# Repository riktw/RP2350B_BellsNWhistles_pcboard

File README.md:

## PCBoard for RP2350B BellsNWhistles

This contains the kicad files for a little board that turns the [RP2350B BellsNWhistles](https://github.com/riktw/RP2350B_BellsNWhistles) board into a small computer.
It has all the modern and some retro IO like:

- 3 x USB
- PS/2 for mouse and keyboard
- NES controller
- Audio via 3.5mm
- MicroSD for storage
- On board RTC

This board is tested and no bugs should remain in the latest version.

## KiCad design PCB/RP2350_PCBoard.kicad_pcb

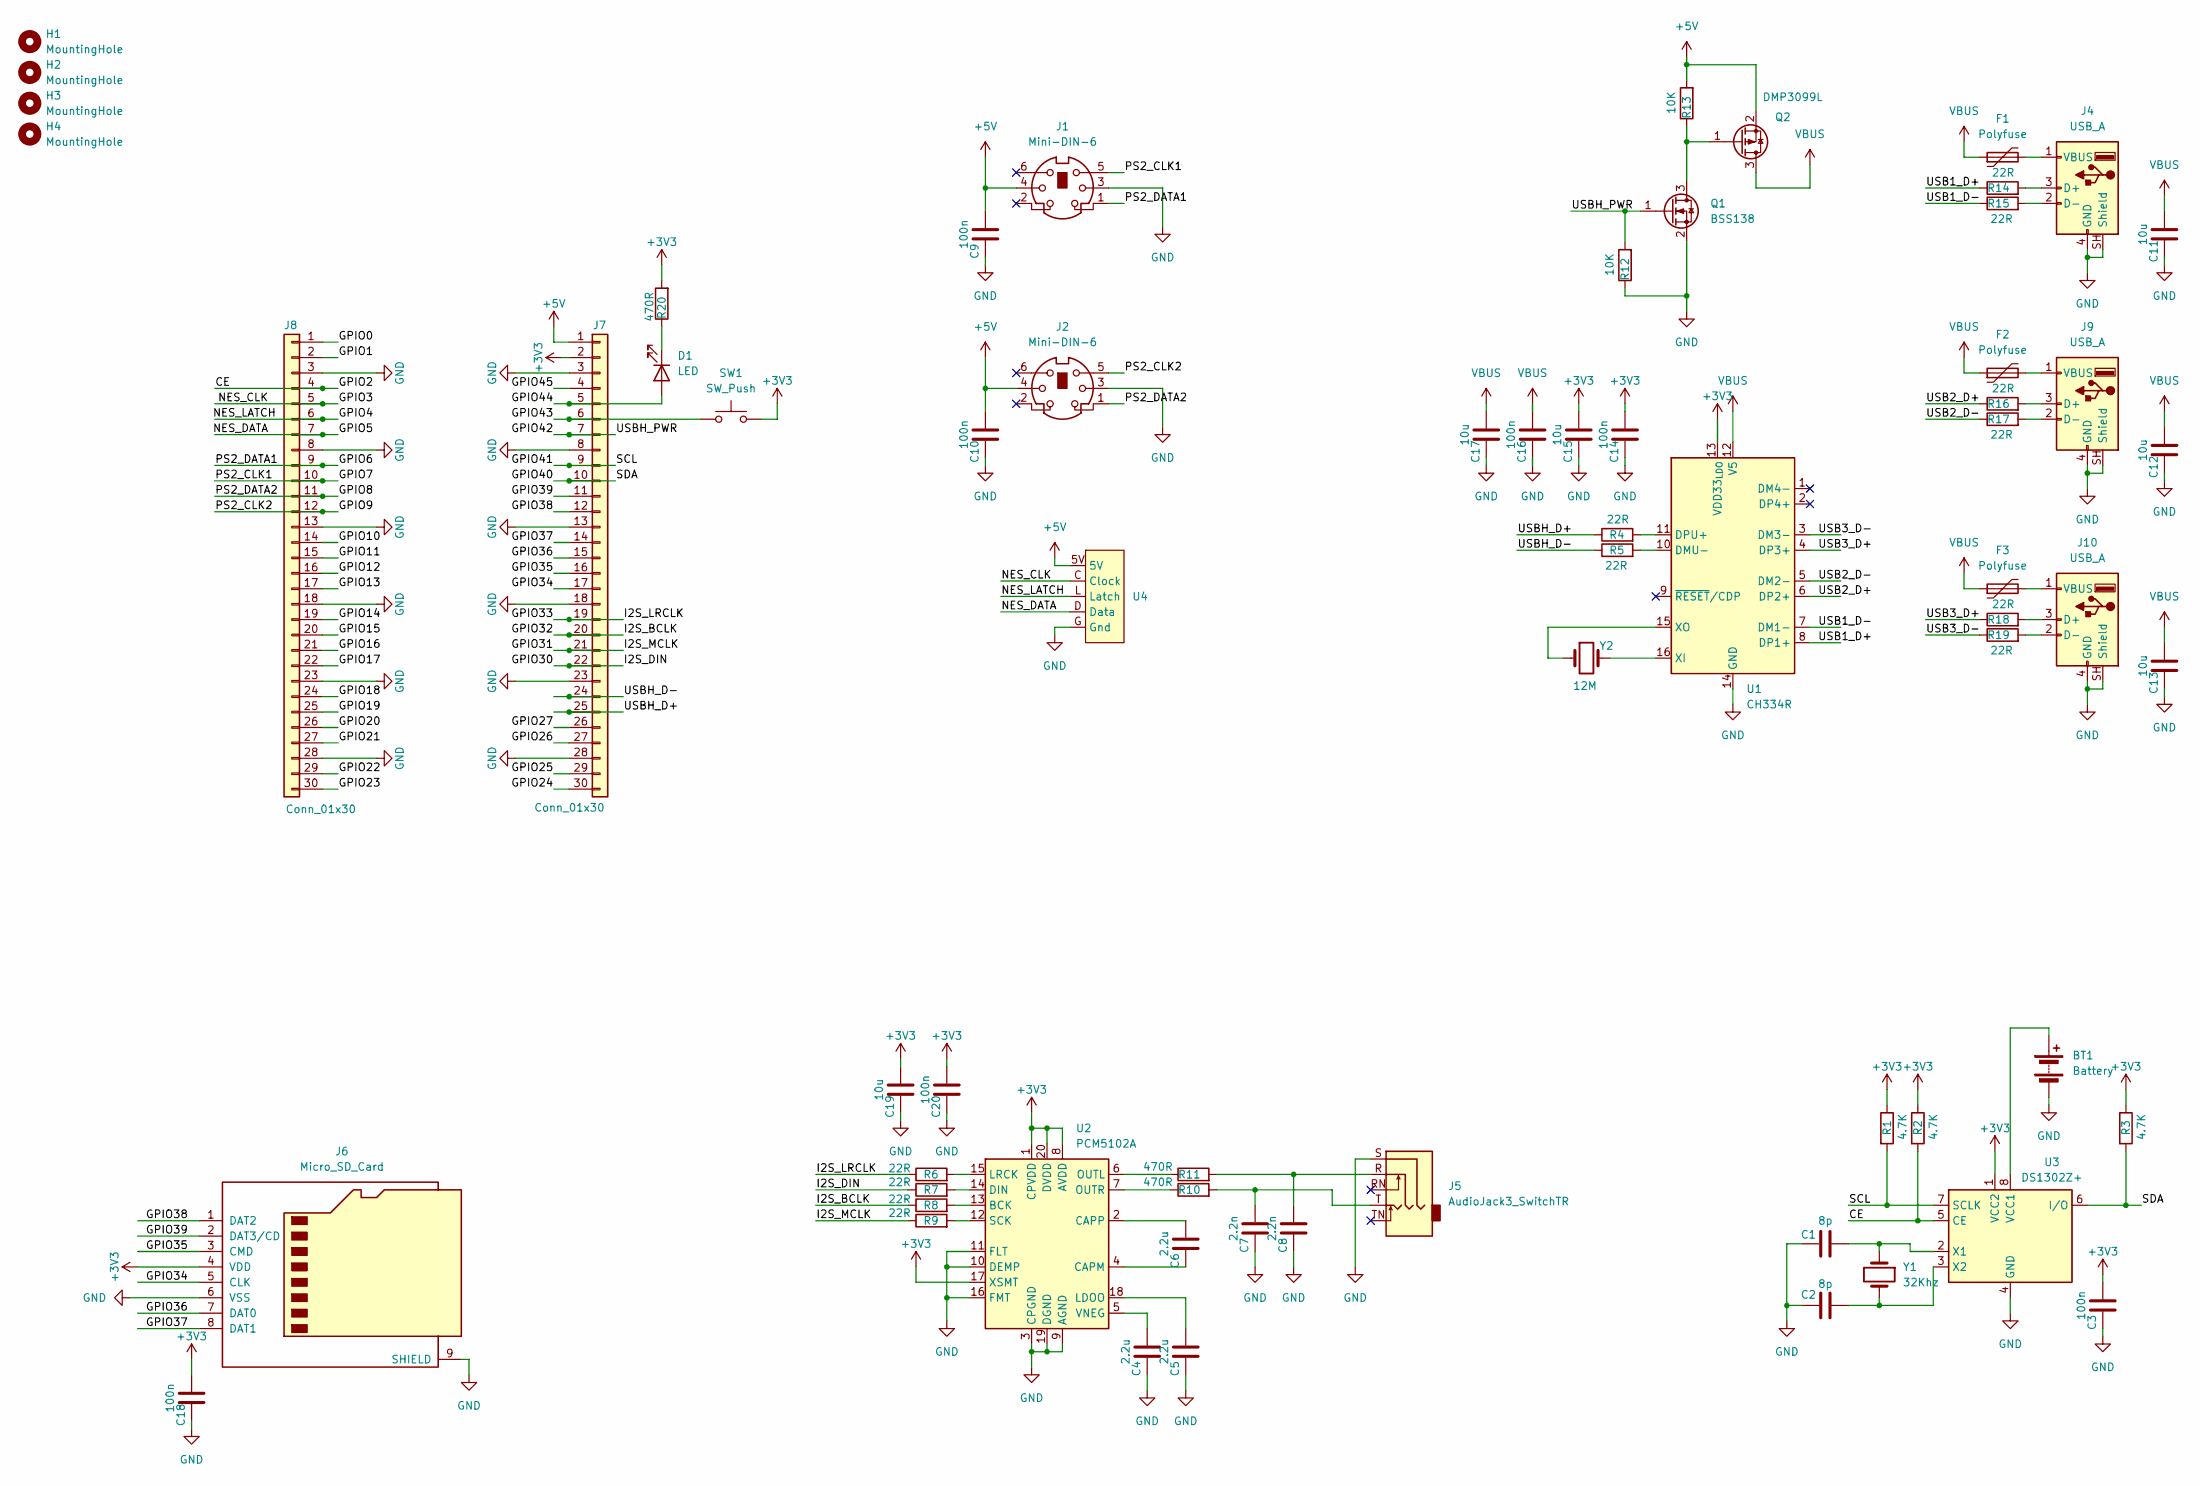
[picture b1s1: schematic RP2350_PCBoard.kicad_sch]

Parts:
BT1: Battery; BatteryHolder_Keystone_1060_1x2032; LCSC C70377
C1, C2: 8p; C_0603_1608Metric_Pad1.08x0.95mm_HandSolder
C3, C9, C10, C14, C16, C18, C20: 100n; C_0603_1608Metric_Pad1.08x0.95mm_HandSolder
C4, C5, C6: 2.2u; C_0603_1608Metric_Pad1.08x0.95mm_HandSolder
C7, C8: 2.2n; C_0603_1608Metric_Pad1.08x0.95mm_HandSolder
C11, C12, C13, C15, C17, C19: 10u; C_0603_1608Metric_Pad1.08x0.95mm_HandSolder
D1: LED; LED_D5.0mm
F1, F2, F3: Polyfuse; C_1812_4532Metric_Pad1.57x3.40mm_HandSolder
H1, H2, H3, H4: MountingHole; MountingHole_3.2mm_M3
J1, J2: Mini-DIN-6; Connector_Mini-DIN_Female_6Pin_2rows
J4, J9, J10: USB_A; USB_A_Molex_67643_Horizontal
J5: AudioJack3_SwitchTR; Jack_3.5mm_CUI_SJ1-3525N_Horizontal
J6: Micro_SD_Card; microSD Hanbo Electronic TF-018; LCSC C961679
J7, J8: Conn_01x30; PinHeader_1x30_P2.54mm_Vertical
Q1: BSS138; SOT-23_Handsoldering; LCSC C82045
Q2: DMP3099L; SOT-23_Handsoldering; LCSC C148354
R1, R2, R3: 4.7K; R_0603_1608Metric_Pad0.98x0.95mm_HandSolder
R4, R5, R6, R7, R8, R9, R14, R15, R16, R17, R18, R19: 22R; R_0603_1608Metric_Pad0.98x0.95mm_HandSolder
R10, R11, R20: 470R; R_0603_1608Metric_Pad0.98x0.95mm_HandSolder
R12, R13: 10K; R_0603_1608Metric_Pad0.98x0.95mm_HandSolder
SW1: SW_Push; SW_PUSH_6mm_H5mm
U1: CH334R; QSOP-16_3.9x4.9mm_P0.635mm; LCSC C4154405
U2: PCM5102A; TSSOP-20_4.4x6.5mm_P0.65mm; LCSC C107671
U3: DS1302Z+; SOIC-8_3.9x4.9mm_P1.27mm; LCSC C8959
U4: NES controller port
Y1: 32Khz; Crystal_DS26_D2.0mm_L6.0mm_Horizontal; LCSC C52082
Y2: 12M; Crystal_SMD_HC49-SD_HandSoldering; LCSC C14871

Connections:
+3V3: C3.2, C14.2, C15.2, C18.2, C19.2, C20.2, J6.4 (VDD), J7.2, R1.1, R2.1, R3.1, R20.2, SW1.2, U1.13 (VDD33_{LDO}), U2.1 (CPVDD), U2.8 (AVDD), U2.17 (XSMT), U2.20 (DVDD), U3.1 (VCC2)
+5V: C9.2, C10.2, J1.4, J2.4, J7.1, Q2.2 (S), R13.2, U4.5V
/CE: J8.4, R2.2, U3.5 (CE)
/GPIO0: J8.1
/GPIO1: J8.2
/GPIO3: J8.5, U4.C (Clock)
/GPIO4: J8.6, U4.L (Latch)
/GPIO5: J8.7, U4.D (Data)
/GPIO6: J1.1, J8.9
/GPIO7: J1.5, J8.10
/GPIO8: J2.1, J8.11
/GPIO9: J2.5, J8.12
/GPIO10: J8.14
/GPIO11: J8.15
/GPIO12: J8.16
/GPIO13: J8.17
/GPIO14: J8.19
/GPIO15: J8.20
/GPIO16: J8.21
/GPIO17: J8.22
/GPIO18: J8.24
/GPIO19: J8.25
/GPIO20: J8.26
/GPIO21: J8.27
/GPIO22: J8.29
/GPIO23: J8.30
/GPIO24: J7.30
/GPIO25: J7.29
/GPIO26: J7.27
/GPIO27: J7.26
/GPIO30: J7.22, R7.1
/GPIO31: J7.21, R9.1
/GPIO32: J7.20, R8.1
/GPIO33: J7.19, R6.1
/GPIO34: J6.5 (CLK), J7.17
/GPIO35: J6.3 (CMD), J7.16
/GPIO36: J6.7 (DAT0), J7.15
/GPIO37: J6.8 (DAT1), J7.14
/GPIO38: J6.1 (DAT2), J7.12
/GPIO39: J6.2 (DAT3/CD), J7.11
/GPIO40: J7.10, R3.2, U3.6 (I/O)
/GPIO41: J7.9, R1.2, U3.7 (SCLK)
/GPIO42: J7.7, Q1.1 (G), R12.2
/GPIO43: J7.6, SW1.1
/GPIO44: D1.2 (A), J7.5
/GPIO45: J7.4
/USB1_D+: R14.1, U1.8 (DP1+)
/USB1_D-: R15.1, U1.7 (DM1-)
/USB2_D+: R16.1, U1.6 (DP2+)
/USB2_D-: R17.1, U1.5 (DM2-)
/USB3_D+: R18.1, U1.4 (DP3+)
/USB3_D-: R19.1, U1.3 (DM3-)
/USBH_D+: J7.25, R4.1
/USBH_D-: J7.24, R5.1
GND: BT1.2 (-), C1.1, C2.1, C3.1, C4.1, C5.1, C7.1, C8.1, C9.1, C10.1, C11.1, C12.1, C13.1, C14.1, C15.1, C16.1, C17.1, C18.1, C19.1, C20.1, J1.3, J2.3, J4.4 (GND), J4.SH (Shield), J5.S, J6.6 (VSS), J6.9 (SHIELD), J7.3, J7.8, J7.13, J7.18, J7.23, J7.28, J8.3, J8.8, J8.13, J8.18, J8.23, J8.28, J9.4 (GND), J9.SH (Shield), J10.4 (GND), J10.SH (Shield), Q1.2 (S), R12.1, U1.14 (GND), U2.3 (CPGND), U2.9 (AGND), U2.10 (DEMP), U2.11 (FLT), U2.16 (FMT), U2.19 (DGND), U3.4 (GND), U4.G (Gnd)
unnamed: BT1.1 (+), U3.8 (VCC1)
unnamed: C7.2, J5.T, R10.2
unnamed: C8.2, J5.R, R11.2
unnamed: D1.1 (K), R20.1
unnamed: J4.3 (D+), R14.2
unnamed: J4.2 (D-), R15.2
unnamed: F1.2, J4.1 (VBUS)
unnamed: J9.3 (D+), R16.2
unnamed: J9.2 (D-), R17.2
unnamed: F2.2, J9.1 (VBUS)
unnamed: J10.3 (D+), R18.2
unnamed: J10.2 (D-), R19.2
unnamed: F3.2, J10.1 (VBUS)
unnamed: Q1.3 (D), Q2.1 (G), R13.1
unnamed: R5.2, U1.10 (DMU-)
unnamed: R4.2, U1.11 (DPU+)
unnamed: U1.16 (XI), Y2.2
unnamed: U1.15 (XO), Y2.1
unnamed: R8.2, U2.13 (BCK)
unnamed: C6.1, U2.4 (CAPM)
unnamed: C6.2, U2.2 (CAPP)
unnamed: R7.2, U2.14 (DIN)
unnamed: C5.2, U2.18 (LDOO)
unnamed: R6.2, U2.15 (LRCK)
unnamed: R11.1, U2.6 (OUTL)
unnamed: R10.1, U2.7 (OUTR)
unnamed: R9.2, U2.12 (SCK)
unnamed: C4.2, U2.5 (VNEG)
unnamed: C1.2, U3.2 (X1), Y1.1
unnamed: C2.2, U3.3 (X2), Y1.2
VBUS: C11.2, C12.2, C13.2, C16.2, C17.2, F1.1, F2.1, F3.1, Q2.3 (D), U1.12 (V5)

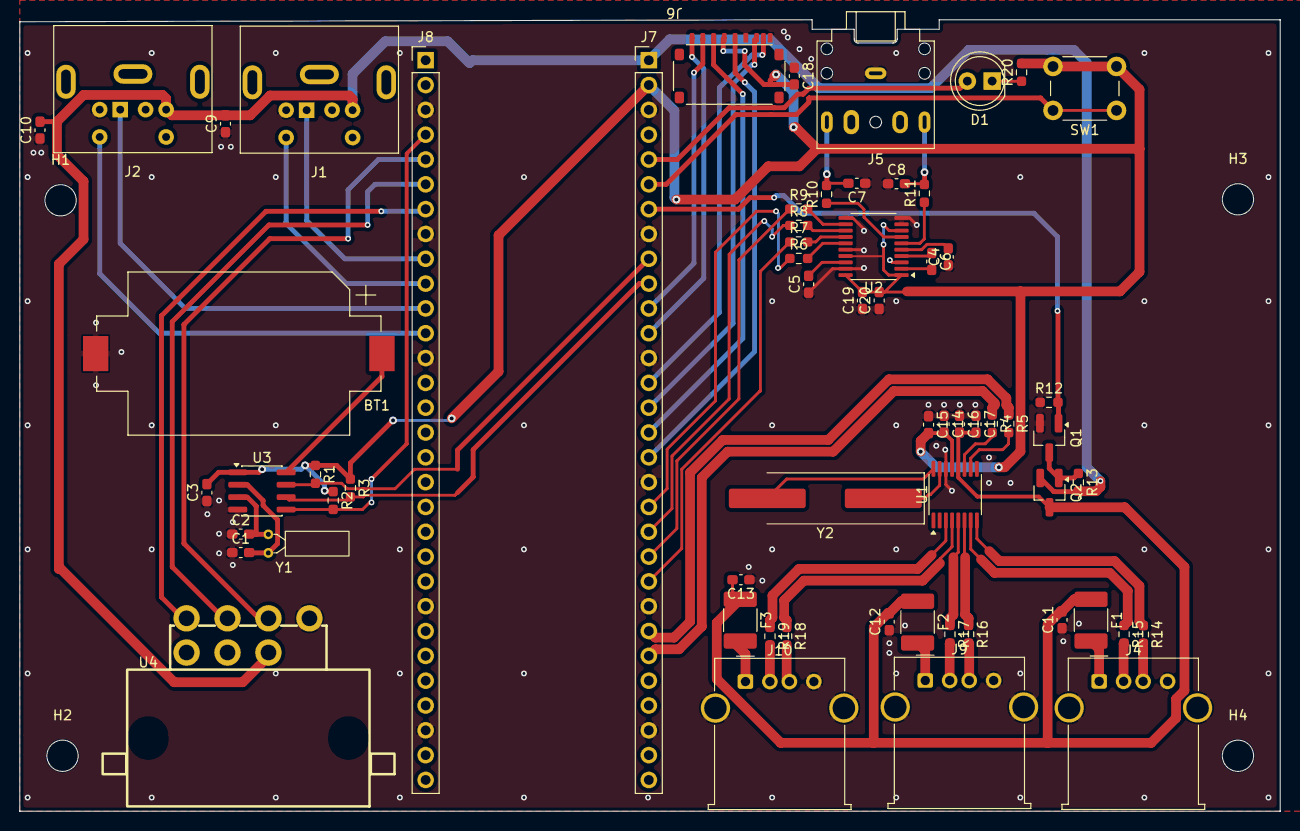
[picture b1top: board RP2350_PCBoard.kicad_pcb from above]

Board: 2 copper layers, 129.0 x 81.0 mm, 67 parts (0 on the bottom side), 65 nets.
